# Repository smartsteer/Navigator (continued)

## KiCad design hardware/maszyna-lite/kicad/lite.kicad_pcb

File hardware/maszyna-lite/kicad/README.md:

# Płytka Maszyna Lite — projekt KiCad 7 (etap 16Lb)

Schemat jako kod i płytka **4‑warstwowa** 170 × 105 mm według `../README.md` (In1 masa, In2 +12 V wyjść). Licencja GPLv3.

| Plik | Co to |
|---|---|
| `lite.py` | schemat (SKiDL) — źródło prawdy; `/usr/bin/python3 lite.py` → `lite.net` |
| `place.py` | obrys i rozmieszczenie (listwy W1–W8 u góry, W9–W15 + LAMPY u dołu, zasilanie/czujniki/CAN/USB z lewej, ESP32 anteną w prawo) |
| `netclass.py` | klasy połączeń: Moc 1,0 mm (V12, wejście), Wyjscia 0,6 mm (A/B zaworów, boczniki), Zasilanie 0,4 mm, sygnały 0,25 mm |
| `smartsteer_lite.pretty` | ESP32‑WROOM‑32D z przelotkami pod padem 0,3 mm (z czasów wersji 2‑warstwowej; zostaje) |
| `mpn.csv` | wartość → MPN (+ LCSC, gdzie znany) do BOM JLCPCB |
| `../produkcja` | Gerber, BOM, CPL dla JLCPCB |

Kolejność (opis narzędzi: `../../narzedzia/README.md`): `lite.py` → kinet2pcb → `netclass.py` → `place.py` →
`plaszczyzny.py lite.kicad_pcb In1.Cu:GND In2.Cu:V12_WYJSCIA` → DSN bez płaszczyzn i bez sieci GND, V12_WYJSCIA, sygnały tylko F/B
→ Freerouting 1.9 → `ses2pcb.py` → `dotrasuj.py --napraw --wewn In2.Cu --plaszczyzny In1.Cu,In2.Cu` (pady masy i +12 V
przelotką do płaszczyzn, resztki) → `strefy_mocy.py lite.kicad_pcb VIN_RAW:4,3,28,35 V12:14,35,44,58` → `drc.py` → `fab_jlcpcb.py`.

Masa i +12 V wyjść nie są prowadzone ścieżkami — każdy pad ma przelotkę do płaszczyzny.

## Zmiany względem specyfikacji 16La

- Przetwornica 12→5 V **LMR33610** (jak pełna płytka, wejście do 36 V) zamiast TPS54202 (28 V) — punkt 4 listy do sprawdzenia.
- Ochrona bramki P‑MOSFET wejścia diodą Zenera 15 V (BZT52C15) — przy zrzucie obciążenia Vgs nie przekroczy 20 V.
- Zasilanie: 2 × 100 µF 35 V (elektrolit SMD) + 10 µF przy każdym mostku.
- **4 warstwy zamiast 2** (2026-11-24): na 2 warstwach masa nie docierała do kilkunastu padów (wyspy wylewki zamknięte ścieżkami).
- Kanały multipleksera: SEKCJA11 → kanał 15, kanał 10 wolny (`MUX_CH` w `lite.py`) — tabela dla firmware 16Lc.

## Do sprawdzenia przez elektronika

1. Lista z `../README.md` (AT8870/DRV8870, prąd 2 A, boczniki, zrzut obciążenia, ADC, listwy, antena, ESD).
2. +12 V wyjść idzie płaszczyzną In2 (1 oz wewnątrz) i przelotkami 0,6 mm do każdego VM — przy wielu zaworach 2‑pin naraz sprawdzić spadek napięcia.
3. Footprint listew 3,5 mm: Phoenix MC 1,5/x‑G‑3,5 (zamiennik Degson 15EDGRC‑3.5) — sprawdzić rozstaw nóżek kupionych gniazd.
4. USB‑C od krawędzi lewej — w skrzynce przez dławik albo zaślepkę.

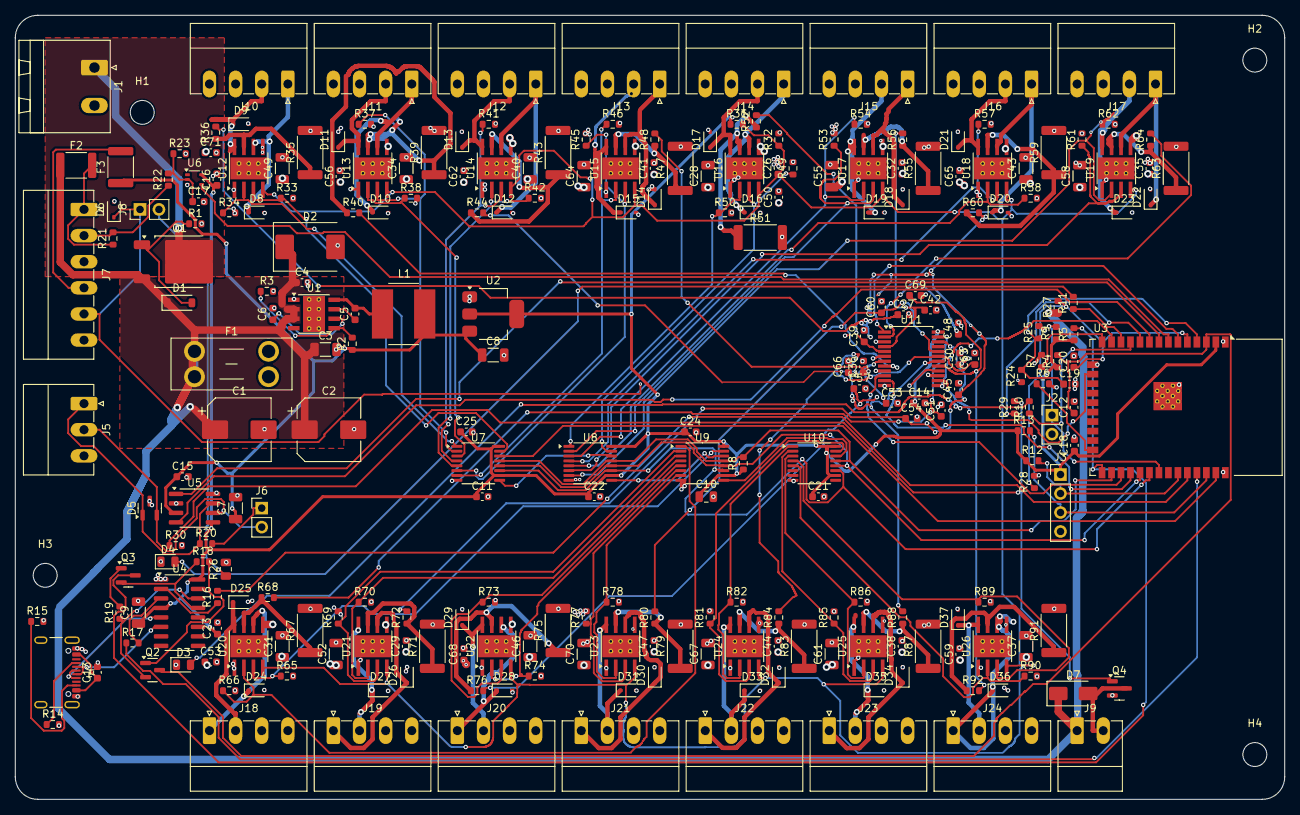
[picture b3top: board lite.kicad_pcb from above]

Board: 4 copper layers, 170.0 x 105.0 mm, 262 parts (0 on the bottom side), 155 nets.

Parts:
C1, C2: 100u 35V 105°C; CP_Elec_8x10
C3, C28, C31, C34, C37, C40, C43, C46, C49, C52, C55, C58, C61, C64, C67, C70: 10u 50V; C_1206_3216Metric
C4, C29, C32, C35, C38, C41, C44, C47, C50, C53, C56, C59, C62, C65, C68, C71: 100n 50V; C_0603_1608Metric
C5, C11, C13, C14, C15, C16, C18, C19, C20, C21, C22, C23, C24, C25, C26: 100n; C_0603_1608Metric
C6, C12, C27, C30, C33, C36, C39, C42, C45, C48, C51, C54, C57, C60, C63, C66, C69: 1u; C_0603_1608Metric
C7, C8, C9: 22u 10V; C_1206_3216Metric
C10: 10u; C_0805_2012Metric
C17: 1n; C_0603_1608Metric
D1: BZT52C15; D_SOD-123
D2: SMCJ24A; D_SMC
D3: LED zielona; LED_0805_2012Metric
D4: LED czerwona; LED_0805_2012Metric
D5: PESD2CAN; SOT-23
D6: PESD5V0S1BA; D_SOD-323
D7: SS14; D_SMA
D8, D9, D10, D11, D12, D13, D14, D15, D16, D17, D18, D19, D20, D21, D22, D23, D24, D25, D26, D27, D28, D29, D30, D31, D32, D33, D34, D35, D36, D37: ESD 24V (np. PESD24VS1UL); D_SOD-323
F1: 10A mini; Fuseholder_Blade_Mini_Keystone_3568
F2: 0.5A; Fuse_1812_4532Metric
F3: 0.2A; Fuse_1812_4532Metric
H1, H2, H3, H4: M3; MountingHole_3.2mm_M3
J1: ZAS +12/masa; PhoenixContact_MSTBA_2,5_2-G-5,08_1x02_P5.08mm_Horizontal
J2: JP CAN/BT; PinHeader_1x02_P2.54mm_Vertical
J3: SERW 3V3/SDA/SCL/GND; PinHeader_1x04_P2.54mm_Vertical
J4: USB-C; USB_C_Receptacle_GCT_USB4105-xx-A_16P_TopMnt_Horizontal
J5: CAN H/L/masa; PhoenixContact_MC_1,5_3-G-3.5_1x03_P3.50mm_Horizontal
J6: JP terminator CAN; PinHeader_1x02_P2.54mm_Vertical
J7: CZUJ przepl +12/syg/masa, cisn +5/syg/masa; PhoenixContact_MC_1,5_6-G-3.5_1x06_P3.50mm_Horizontal
J8: JP 4-20mA; PinHeader_1x02_P2.54mm_Vertical
J9: LAMPY +12/cewka; PhoenixContact_MC_1,5_2-G-3.5_1x02_P3.50mm_Horizontal
J10: W1 SEKCJA1 A/B/+12/masa; PhoenixContact_MC_1,5_4-G-3.5_1x04_P3.50mm_Horizontal
J11: W2 SEKCJA2 A/B/+12/masa; PhoenixContact_MC_1,5_4-G-3.5_1x04_P3.50mm_Horizontal
J12: W3 SEKCJA3 A/B/+12/masa; PhoenixContact_MC_1,5_4-G-3.5_1x04_P3.50mm_Horizontal
J13: W4 SEKCJA4 A/B/+12/masa; PhoenixContact_MC_1,5_4-G-3.5_1x04_P3.50mm_Horizontal
J14: W5 SEKCJA5 A/B/+12/masa; PhoenixContact_MC_1,5_4-G-3.5_1x04_P3.50mm_Horizontal
J15: W6 SEKCJA6 A/B/+12/masa; PhoenixContact_MC_1,5_4-G-3.5_1x04_P3.50mm_Horizontal
J16: W7 SEKCJA7 A/B/+12/masa; PhoenixContact_MC_1,5_4-G-3.5_1x04_P3.50mm_Horizontal
J17: W8 SEKCJA8 A/B/+12/masa; PhoenixContact_MC_1,5_4-G-3.5_1x04_P3.50mm_Horizontal
J18: W9 SEKCJA9 A/B/+12/masa; PhoenixContact_MC_1,5_4-G-3.5_1x04_P3.50mm_Horizontal
J19: W10 SEKCJA10 A/B/+12/masa; PhoenixContact_MC_1,5_4-G-3.5_1x04_P3.50mm_Horizontal
J20: W11 SEKCJA11 A/B/+12/masa; PhoenixContact_MC_1,5_4-G-3.5_1x04_P3.50mm_Horizontal
J21: W12 SEKCJA12 A/B/+12/masa; PhoenixContact_MC_1,5_4-G-3.5_1x04_P3.50mm_Horizontal
J22: W13 SEKCJA13 A/B/+12/masa; PhoenixContact_MC_1,5_4-G-3.5_1x04_P3.50mm_Horizontal
J23: W14 ZAW_GLOWNY A/B/+12/masa; PhoenixContact_MC_1,5_4-G-3.5_1x04_P3.50mm_Horizontal
J24: W15 ZAW_REG A/B/+12/masa; PhoenixContact_MC_1,5_4-G-3.5_1x04_P3.50mm_Horizontal
L1: 10uH 2A; L_Bourns_SRN8040TA
Q1: AOD4185; TO-252-2
Q2, Q3: MMBT3904; SOT-23
Q4: AO3400A; SOT-23
R1, R4, R5, R6, R7, R8, R9, R18, R19, R22, R24, R33, R34, R37, R38, R41, R42, R45, R46, R49, R50, R53, R54, R57, R58, R61, R62, R65, R66, R69, R70, R73, R74, R77, R78, R81, R82, R85, R86, R89, R90: 10k; R_0603_1608Metric
R2, R27, R30: 100k; R_0603_1608Metric
R3: 24k9; R_0603_1608Metric
R10, R11, R36, R40, R44, R48, R52, R56, R60, R64, R68, R72, R76, R80, R84, R88, R92: 1k; R_0603_1608Metric
R12, R13, R21, R23: 4k7; R_0603_1608Metric
R14, R15: 5k1; R_0603_1608Metric
R16, R17: 470; R_0603_1608Metric
R20: 120; R_0603_1608Metric
R25, R32: 20k; R_0603_1608Metric
R26: 150 0.1%; R_0805_2012Metric
R28: 15k; R_0603_1608Metric
R29: 100; R_0603_1608Metric
R31: 2k; R_0603_1608Metric
R35, R39, R43, R47, R51, R55, R59, R63, R67, R71, R75, R79, R83, R87, R91: 0R15 1W; R_2512_6332Metric
U1: LMR33610ADDAR; Texas_HSOP-8-1EP_3.9x4.9mm_P1.27mm_ThermalVias
U2: AMS1117-3.3; SOT-223-3_TabPin2
U3: ESP32-WROOM-32E-N4; ESP32-WROOM-32D_Przelotki0.3
U4: CH340C; SOIC-16_3.9x9.9mm_P1.27mm
U5: TJA1051T/3; SOIC-8_3.9x4.9mm_P1.27mm
U6: 74LVC1G17; SOT-353_SC-70-5
U7, U8, U9, U10: 74HC595PW; TSSOP-16_4.4x5mm_P0.65mm
U11: CD74HC4067SM96; SSOP-24_5.3x8.2mm_P0.65mm
U12, U13, U14, U15, U16, U17, U18, U19, U20, U21, U22, U23, U24, U25, U26: DRV8870DDAR; Texas_HTSOP-8-1EP_3.9x4.9mm_P1.27mm_EP2.95x4.9mm_Mask2.4x3.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

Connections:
AR_B1: Q2.1, R18.2
AR_B2: Q3.1, R19.2
BUCK_BOOT: C5.1, U1.7
BUCK_FB: R2.2, R3.1, U1.5
BUCK_SW: C5.2, L1.1, U1.8
BUCK_VCC: C6.1, U1.6
CANH: D5.1, J5.1, R20.1, U5.7
CANL: D5.2, J5.2, J6.2, U5.6
CAN_RX: U3.9, U5.4
CAN_TERM: J6.1, R20.2
CAN_TX: U3.8, U5.1
CISN_ADC: C19.1, R24.2, R25.1, U3.4
CISN_SHUNT: J8.2, R26.1
CISN_SYG: D6.1, J7.5, J8.1, R24.1
DRV_VREF: C26.1, R31.2, R32.1, U12.4, U13.4, U14.4, U15.4, U16.4, U17.4, U18.4, U19.4, U20.4, U21.4, U22.4, U23.4, U24.4, U25.4, U26.4
ESP_EN: C12.1, Q2.3, R4.2, U3.3
ESP_IO0: Q3.3, R5.2, U3.25
ESP_IO2: R6.1, U3.24
ESP_IO12: R7.1, U3.14
FLOW_3V3: U3.7, U6.4
GND: C1.2, C2.2, C3.2, C4.2, C6.2, C7.2, C8.2, C9.2, C10.2, C11.2, C12.2, C13.2, C14.2, C15.2, C16.2, C17.2, C18.2, C19.2, C20.2, C21.2, C22.2, C23.2, C24.2, C25.2, C26.2, C27.2, C28.2, C29.2, C30.2, C31.2, C32.2, C33.2, C34.2, C35.2, C36.2, C37.2, C38.2, C39.2, C40.2, C41.2, C42.2, C43.2, C44.2, C45.2, C46.2, C47.2, C48.2, C49.2, C50.2, C51.2, C52.2, C53.2, C54.2, C55.2, C56.2, C57.2, C58.2, C59.2, C60.2, C61.2, C62.2, C63.2, C64.2, C65.2, C66.2, C67.2, C68.2, C69.2, C70.2, C71.2, D2.2, D3.1, D4.1, D5.3, D6.2, D8.2, D9.2, D10.2, D11.2, D12.2, D13.2, D14.2, D15.2, D16.2, D17.2, D18.2, D19.2, D20.2, D21.2, D22.2, D23.2, D24.2, D25.2, D26.2, D27.2, D28.2, D29.2, D30.2, D31.2, D32.2, D33.2, D34.2, D35.2, D36.2, D37.2, J1.2, J2.2, J3.4, J4.A1, J4.A12, J4.B1, J4.B12, J4.S1, J5.3, J7.3, J7.6, J10.4, J11.4, J12.4, J13.4, J14.4, J15.4, J16.4, J17.4, J18.4, J19.4, J20.4, J21.4, J22.4, J23.4, J24.4, Q4.2, R1.2, R3.2, R6.2, R7.2, R14.2, R15.2, R23.2, R25.2, R26.2, R28.2, R30.2, R32.2, R33.2, R34.2, R35.2, R37.2, R38.2, R39.2, R41.2, R42.2, R43.2, R45.2, R46.2, R47.2, R49.2, R50.2, R51.2, R53.2, R54.2, R55.2, R57.2, R58.2, R59.2, R61.2, R62.2, R63.2, R65.2, R66.2, R67.2, R69.2, R70.2, R71.2, R73.2, R74.2, R75.2, R77.2, R78.2, R79.2, R81.2, R82.2, R83.2, R85.2, R86.2, R87.2, R89.2, R90.2, R91.2, U1.1, U1.9, U2.1, U3.1, U3.15, U3.38, U3.39, U4.1, U5.2, U5.8, U6.3, U7.8, U8.8, U9.8, U10.8, U11.12, U11.15, U12.1, U12.9, U13.1, U13.9, U14.1, U14.9, U15.1, U15.9, U16.1, U16.9, U17.1, U17.9, U18.1, U18.9, U19.1, U19.9, U20.1, U20.9, U21.1, U21.9, U22.1, U22.9, U23.1, U23.9, U24.1, U24.9, U25.1, U25.9, U26.1, U26.9
I2C_SCL: J3.3, R13.2, U3.36
I2C_SDA: J3.2, R12.2, U3.33
JP_CAN: J2.1, R9.2, U3.31
LAMPA_CEWKA: D7.2, J9.2, Q4.3
LAMP_G: Q4.1, R29.2, R30.1
LAMP_IN: R29.1, U3.10
LED_A_czerwona: D4.2, R11.2
LED_A_zielona: D3.2, R10.2
LED_CZERWONA: R11.1, U3.12
LED_ZIELONA: R10.1, U3.11
MUX_ADC: U3.6, U11.1
MUX_S0: U3.27, U11.10
MUX_S1: U3.28, U11.11
MUX_S2: U3.16, U11.14
MUX_S3: U3.13, U11.13
unnamed: J4.A5, R14.1
unnamed: J4.B5, R15.1
unnamed: R16.1, U4.2
unnamed: R17.2, U4.3
unnamed: F2.2, J7.1, R21.1
unnamed: F3.2, J7.4
PRZEPL_DZ: C17.1, R22.2, R23.1, U6.2
PRZEPL_SYG: J7.2, R21.2, R22.1
Q1_G: D1.2, Q1.1, R1.1
REG_RCLK: U3.29, U7.12, U8.12, U9.12, U10.12
REG_nOE: R8.2, U3.26, U7.13, U8.13, U9.13, U10.13
SEKCJA1_A: D8.1, J10.1, U12.6
SEKCJA1_B: D9.1, J10.2, U12.8
SEKCJA1_IN1: R33.1, U7.15, U12.3
SEKCJA1_IN2: R34.1, U7.1, U12.2
SEKCJA1_IPOM: C27.1, R36.2, U11.9
SEKCJA1_ISEN: R35.1, R36.1, U12.7
SEKCJA2_A: D10.1, J11.1, U13.6
SEKCJA2_B: D11.1, J11.2, U13.8
SEKCJA2_IN1: R37.1, U7.2, U13.3
SEKCJA2_IN2: R38.1, U7.3, U13.2
SEKCJA2_IPOM: C30.1, R40.2, U11.8
SEKCJA2_ISEN: R39.1, R40.1, U13.7
SEKCJA3_A: D12.1, J12.1, U14.6
SEKCJA3_B: D13.1, J12.2, U14.8
SEKCJA3_IN1: R41.1, U7.4, U14.3
SEKCJA3_IN2: R42.1, U7.5, U14.2
SEKCJA3_IPOM: C33.1, R44.2, U11.7
SEKCJA3_ISEN: R43.1, R44.1, U14.7
SEKCJA4_A: D14.1, J13.1, U15.6
SEKCJA4_B: D15.1, J13.2, U15.8
SEKCJA4_IN1: R45.1, U7.6, U15.3
SEKCJA4_IN2: R46.1, U7.7, U15.2
SEKCJA4_IPOM: C36.1, R48.2, U11.6
SEKCJA4_ISEN: R47.1, R48.1, U15.7
SEKCJA5_A: D16.1, J14.1, U16.6
SEKCJA5_B: D17.1, J14.2, U16.8
SEKCJA5_IN1: R49.1, U8.15, U16.3
SEKCJA5_IN2: R50.1, U8.1, U16.2
SEKCJA5_IPOM: C39.1, R52.2, U11.5
SEKCJA5_ISEN: R51.1, R52.1, U16.7
SEKCJA6_A: D18.1, J15.1, U17.6
SEKCJA6_B: D19.1, J15.2, U17.8
SEKCJA6_IN1: R53.1, U8.2, U17.3
SEKCJA6_IN2: R54.1, U8.3, U17.2
SEKCJA6_IPOM: C42.1, R56.2, U11.4
SEKCJA6_ISEN: R55.1, R56.1, U17.7
SEKCJA7_A: D20.1, J16.1, U18.6
SEKCJA7_B: D21.1, J16.2, U18.8
SEKCJA7_IN1: R57.1, U8.4, U18.3
SEKCJA7_IN2: R58.1, U8.5, U18.2
SEKCJA7_IPOM: C45.1, R60.2, U11.3
SEKCJA7_ISEN: R59.1, R60.1, U18.7
SEKCJA8_A: D22.1, J17.1, U19.6
SEKCJA8_B: D23.1, J17.2, U19.8
SEKCJA8_IN1: R61.1, U8.6, U19.3
SEKCJA8_IN2: R62.1, U8.7, U19.2
SEKCJA8_IPOM: C48.1, R64.2, U11.2
SEKCJA8_ISEN: R63.1, R64.1, U19.7
SEKCJA9_A: D24.1, J18.1, U20.6
SEKCJA9_B: D25.1, J18.2, U20.8
SEKCJA9_IN1: R65.1, U9.15, U20.3
SEKCJA9_IN2: R66.1, U9.1, U20.2
SEKCJA9_IPOM: C51.1, R68.2, U11.23
SEKCJA9_ISEN: R67.1, R68.1, U20.7
SEKCJA10_A: D26.1, J19.1, U21.6
SEKCJA10_B: D27.1, J19.2, U21.8
SEKCJA10_IN1: R69.1, U9.2, U21.3
SEKCJA10_IN2: R70.1, U9.3, U21.2
SEKCJA10_IPOM: C54.1, R72.2, U11.22
SEKCJA10_ISEN: R71.1, R72.1, U21.7
SEKCJA11_A: D28.1, J20.1, U22.6
SEKCJA11_B: D29.1, J20.2, U22.8
SEKCJA11_IN1: R73.1, U9.4, U22.3
SEKCJA11_IN2: R74.1, U9.5, U22.2
SEKCJA11_IPOM: C57.1, R76.2, U11.16
SEKCJA11_ISEN: R75.1, R76.1, U22.7
SEKCJA12_A: D30.1, J21.1, U23.6
SEKCJA12_B: D31.1, J21.2, U23.8
SEKCJA12_IN1: R77.1, U9.6, U23.3
SEKCJA12_IN2: R78.1, U9.7, U23.2
SEKCJA12_IPOM: C60.1, R80.2, U11.20
SEKCJA12_ISEN: R79.1, R80.1, U23.7
SEKCJA13_A: D32.1, J22.1, U24.6
SEKCJA13_B: D33.1, J22.2, U24.8
SEKCJA13_IN1: R81.1, U10.15, U24.3
SEKCJA13_IN2: R82.1, U10.1, U24.2
SEKCJA13_IPOM: C63.1, R84.2, U11.19
SEKCJA13_ISEN: R83.1, R84.1, U24.7
SPI_MOSI: U3.37, U7.14
SPI_SCK: U3.30, U7.11, U8.11, U9.11, U10.11
SR_CHAIN0: U7.9, U8.14
SR_CHAIN1: U8.9, U9.14
SR_CHAIN2: U9.9, U10.14
U0RXD: R16.2, U3.34
U0TXD: R17.1, U3.35
USB_DM: J4.A7, J4.B7, U4.6
USB_DP: J4.A6, J4.B6, U4.5
USB_DTR: Q3.2, R18.1, U4.13
USB_RTS: Q2.2, R19.1, U4.14
USB_VBUS: C13.1, J4.A4, J4.A9, J4.B4, J4.B9
V3V3: C9.1, C10.1, C11.1, C14.1, C16.1, C18.1, C21.1, C22.1, C23.1, C24.1, C25.1, J3.1, R4.1, R5.1, R8.1, R9.1, R12.1, R13.1, R31.1, U2.2, U3.2, U4.4, U4.16, U5.5, U6.5, U7.10, U7.16, U8.10, U8.16, U9.10, U9.16, U10.10, U10.16, U11.24
V5: C7.1, C8.1, C15.1, F3.1, L1.2, R2.1, U2.3, U5.3
V12: C1.1, C2.1, C3.1, C4.1, D1.1, D2.1, D7.1, F1.1, F2.1, J9.1, Q1.3, R27.1, U1.2, U1.3
V12_WYJSCIA: C28.1, C29.1, C31.1, C32.1, C34.1, C35.1, C37.1, C38.1, C40.1, C41.1, C43.1, C44.1, C46.1, C47.1, C49.1, C50.1, C52.1, C53.1, C55.1, C56.1, C58.1, C59.1, C61.1, C62.1, C64.1, C65.1, C67.1, C68.1, C70.1, C71.1, F1.2, J10.3, J11.3, J12.3, J13.3, J14.3, J15.3, J16.3, J17.3, J18.3, J19.3, J20.3, J21.3, J22.3, J23.3, J24.3, U12.5, U13.5, U14.5, U15.5, U16.5, U17.5, U18.5, U19.5, U20.5, U21.5, U22.5, U23.5, U24.5, U25.5, U26.5
VIN_RAW: J1.1, Q1.2
ZAS_ADC: C20.1, R27.2, R28.1, U3.5
ZAW_GLOWNY_A: D34.1, J23.1, U25.6
ZAW_GLOWNY_B: D35.1, J23.2, U25.8
ZAW_GLOWNY_IN1: R85.1, U10.2, U25.3
ZAW_GLOWNY_IN2: R86.1, U10.3, U25.2
ZAW_GLOWNY_IPOM: C66.1, R88.2, U11.18
ZAW_GLOWNY_ISEN: R87.1, R88.1, U25.7
ZAW_REG_A: D36.1, J24.1, U26.6
ZAW_REG_B: D37.1, J24.2, U26.8
ZAW_REG_IN1: R89.1, U10.4, U26.3
ZAW_REG_IN2: R90.1, U10.5, U26.2
ZAW_REG_IPOM: C69.1, R92.2, U11.17
ZAW_REG_ISEN: R91.1, R92.1, U26.7

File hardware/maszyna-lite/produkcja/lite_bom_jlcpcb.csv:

Comment,Designator,Footprint,MPN,LCSC Part #
0.2A,F3,Fuse_1812_4532Metric,SMD1812P020TF,
0.5A,F2,Fuse_1812_4532Metric,SMD1812P050TF,
0R15 1W,"R35,R39,R43,R47,R51,R55,R59,R63,R67,R71,R75,R79,R83,R87,R91",R_2512_6332Metric,PE2512FKE070R15L,
100,R29,R_0603_1608Metric,0603WAF1000T5E,
100k,"R2,R27,R30",R_0603_1608Metric,0603WAF1003T5E,C25803
100n,"C5,C11,C13,C14,C15,C16,C18,C19,C20,C21,C22,C23,C24,C25,C26",C_0603_1608Metric,CC0603KRX7R9BB104,C14663
100n 50V,"C4,C29,C32,C35,C38,C41,C44,C47,C50,C53,C56,C59,C62,C65,C68,C71",C_0603_1608Metric,CC0603KRX7R9BB104,C14663
100u 35V 105°C,"C1,C2",CP_Elec_8x10,(elektrolit SMD 8×10 100 µF 35 V 105 °C),
10A mini,F1,Fuseholder_Blade_Mini_Keystone_3568,Keystone 3568 + bezpiecznik mini 10 A,
10k,"R1,R4,R5,R6,R7,R8,R9,R18,R19,R22,R24,R33,R34,R37,R38,R41,R42,R45,R46,R49,R50,R53,R54,R57,R58,R61,R62,R65,R66,R69,R70,R73,R74,R77,R78,R81,R82,R85,R86,R89,R90",R_0603_1608Metric,0603WAF1002T5E,C25804
10u,C10,C_0805_2012Metric,CL21A106KAYNNNE,C15850
10u 50V,"C3,C28,C31,C34,C37,C40,C43,C46,C49,C52,C55,C58,C61,C64,C67,C70",C_1206_3216Metric,CL31B106KBHNNNE,
10uH 2A,L1,L_Bourns_SRN8040TA,SRN8040TA-100M,
120,R20,R_0603_1608Metric,0603WAF1200T5E,
150 0.1%,R26,R_0805_2012Metric,"(150 Ω 0,1 % 0805)",
15k,R28,R_0603_1608Metric,0603WAF1502T5E,
1k,"R10,R11,R36,R40,R44,R48,R52,R56,R60,R64,R68,R72,R76,R80,R84,R88,R92",R_0603_1608Metric,0603WAF1001T5E,
1n,C17,C_0603_1608Metric,CL10B102KB8NNNC,
1u,"C6,C12,C27,C30,C33,C36,C39,C42,C45,C48,C51,C54,C57,C60,C63,C66,C69",C_0603_1608Metric,CL10B105KO8NNNC,
20k,"R25,R32",R_0603_1608Metric,0603WAF2002T5E,
22u 10V,"C7,C8,C9",C_1206_3216Metric,CL31A226KAHNNNE,
24k9,R3,R_0603_1608Metric,0603WAF2492T5E,
2k,R31,R_0603_1608Metric,0603WAF2001T5E,
470,"R16,R17",R_0603_1608Metric,0603WAF4700T5E,
4k7,"R12,R13,R21,R23",R_0603_1608Metric,0603WAF4701T5E,C23162
5k1,"R14,R15",R_0603_1608Metric,0603WAF5101T5E,
74HC595PW,"U7,U8,U9,U10",TSSOP-16_4.4x5mm_P0.65mm,"74HC595PW,118",
74LVC1G17,U6,SOT-353_SC-70-5,"74LVC1G17GW,125",
AMS1117-3.3,U2,SOT-223-3_TabPin2,AMS1117-3.3,C6186
AO3400A,Q4,SOT-23,AO3400A,C20917
AOD4185,Q1,TO-252-2,AOD4185,
BZT52C15,D1,D_SOD-123,BZT52C15,
CAN H/L/masa,J5,"PhoenixContact_MC_1,5_3-G-3.5_1x03_P3.50mm_Horizontal",,
CD74HC4067SM96,U11,SSOP-24_5.3x8.2mm_P0.65mm,CD74HC4067SM96,
CH340C,U4,SOIC-16_3.9x9.9mm_P1.27mm,CH340C,C84681
"CZUJ przepl +12/syg/masa, cisn +5/syg/masa",J7,"PhoenixContact_MC_1,5_6-G-3.5_1x06_P3.50mm_Horizontal",,
DRV8870DDAR,"U12,U13,U14,U15,U16,U17,U18,U19,U20,U21,U22,U23,U24,U25,U26",Texas_HTSOP-8-1EP_3.9x4.9mm_P1.27mm_EP2.95x4.9mm_Mask2.4x3.1mm_ThermalVias,DRV8870DDAR,
ESD 24V (np. PESD24VS1UL),"D8,D9,D10,D11,D12,D13,D14,D15,D16,D17,D18,D19,D20,D21,D22,D23,D24,D25,D26,D27,D28,D29,D30,D31,D32,D33,D34,D35,D36,D37",D_SOD-323,"PESD24VS1UL,315",
ESP32-WROOM-32E-N4,U3,ESP32-WROOM-32D_Przelotki0.3,ESP32-WROOM-32E-N4,
JP 4-20mA,J8,PinHeader_1x02_P2.54mm_Vertical,,
JP CAN/BT,J2,PinHeader_1x02_P2.54mm_Vertical,,
JP terminator CAN,J6,PinHeader_1x02_P2.54mm_Vertical,,
LAMPY +12/cewka,J9,"PhoenixContact_MC_1,5_2-G-3.5_1x02_P3.50mm_Horizontal",,
LED czerwona,D4,LED_0805_2012Metric,(LED 0805 czerwona),
LED zielona,D3,LED_0805_2012Metric,(LED 0805 zielona),
LMR33610ADDAR,U1,Texas_HSOP-8-1EP_3.9x4.9mm_P1.27mm_ThermalVias,LMR33610ADDAR,
MMBT3904,"Q2,Q3",SOT-23,MMBT3904,C20526
PESD2CAN,D5,SOT-23,"PESD2CAN,215",
PESD5V0S1BA,D6,D_SOD-323,"PESD5V0S1BA,115",
SERW 3V3/SDA/SCL/GND,J3,PinHeader_1x04_P2.54mm_Vertical,,
SMCJ24A,D2,D_SMC,SMCJ24A,
SS14,D7,D_SMA,SS14,C2480
TJA1051T/3,U5,SOIC-8_3.9x4.9mm_P1.27mm,"TJA1051T/3,118",C38695
USB-C,J4,USB_C_Receptacle_GCT_USB4105-xx-A_16P_TopMnt_Horizontal,USB4105-GF-A,
W1 SEKCJA1 A/B/+12/masa,J10,"PhoenixContact_MC_1,5_4-G-3.5_1x04_P3.50mm_Horizontal",,
W10 SEKCJA10 A/B/+12/masa,J19,"PhoenixContact_MC_1,5_4-G-3.5_1x04_P3.50mm_Horizontal",,
W11 SEKCJA11 A/B/+12/masa,J20,"PhoenixContact_MC_1,5_4-G-3.5_1x04_P3.50mm_Horizontal",,
W12 SEKCJA12 A/B/+12/masa,J21,"PhoenixContact_MC_1,5_4-G-3.5_1x04_P3.50mm_Horizontal",,
W13 SEKCJA13 A/B/+12/masa,J22,"PhoenixContact_MC_1,5_4-G-3.5_1x04_P3.50mm_Horizontal",,
W14 ZAW_GLOWNY A/B/+12/masa,J23,"PhoenixContact_MC_1,5_4-G-3.5_1x04_P3.50mm_Horizontal",,
W15 ZAW_REG A/B/+12/masa,J24,"PhoenixContact_MC_1,5_4-G-3.5_1x04_P3.50mm_Horizontal",,
W2 SEKCJA2 A/B/+12/masa,J11,"PhoenixContact_MC_1,5_4-G-3.5_1x04_P3.50mm_Horizontal",,
W3 SEKCJA3 A/B/+12/masa,J12,"PhoenixContact_MC_1,5_4-G-3.5_1x04_P3.50mm_Horizontal",,
W4 SEKCJA4 A/B/+12/masa,J13,"PhoenixContact_MC_1,5_4-G-3.5_1x04_P3.50mm_Horizontal",,
W5 SEKCJA5 A/B/+12/masa,J14,"PhoenixContact_MC_1,5_4-G-3.5_1x04_P3.50mm_Horizontal",,
W6 SEKCJA6 A/B/+12/masa,J15,"PhoenixContact_MC_1,5_4-G-3.5_1x04_P3.50mm_Horizontal",,
W7 SEKCJA7 A/B/+12/masa,J16,"PhoenixContact_MC_1,5_4-G-3.5_1x04_P3.50mm_Horizontal",,
W8 SEKCJA8 A/B/+12/masa,J17,"PhoenixContact_MC_1,5_4-G-3.5_1x04_P3.50mm_Horizontal",,
W9 SEKCJA9 A/B/+12/masa,J18,"PhoenixContact_MC_1,5_4-G-3.5_1x04_P3.50mm_Horizontal",,
ZAS +12/masa,J1,"PhoenixContact_MSTBA_2,5_2-G-5,08_1x02_P5.08mm_Horizontal",,
